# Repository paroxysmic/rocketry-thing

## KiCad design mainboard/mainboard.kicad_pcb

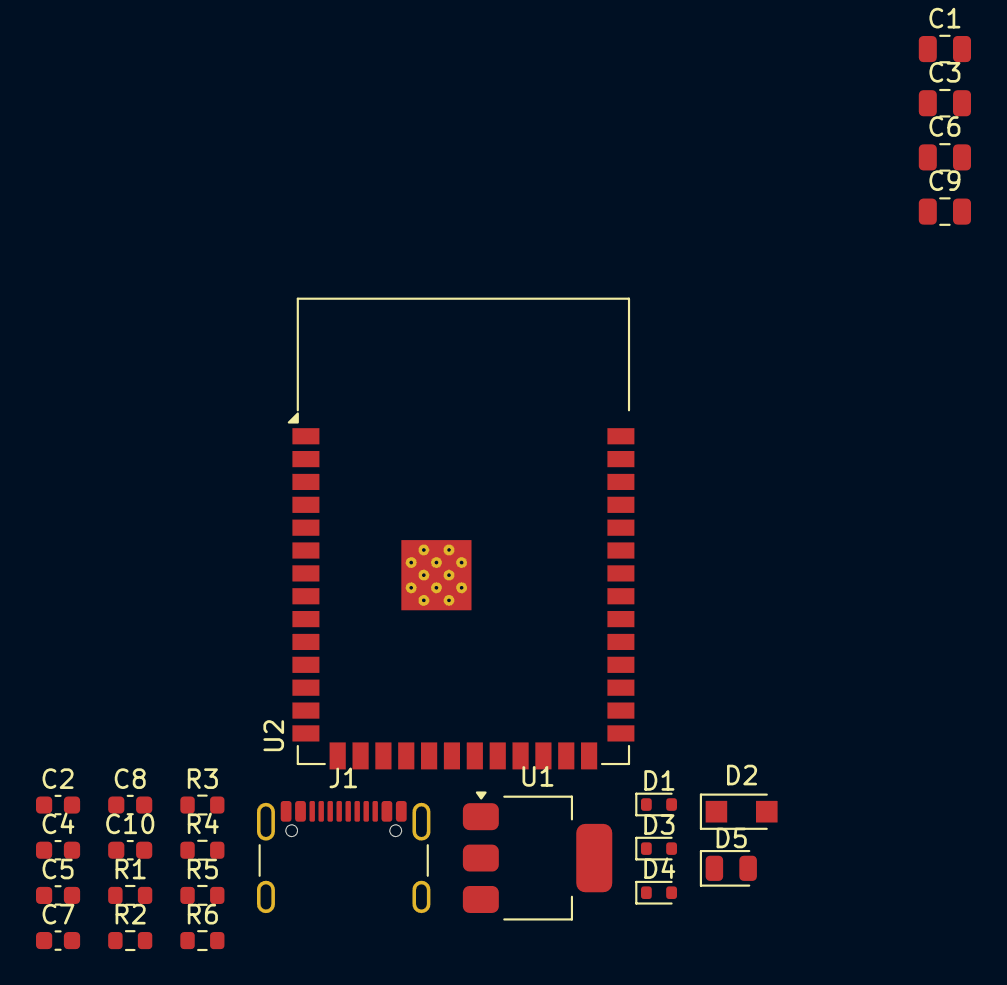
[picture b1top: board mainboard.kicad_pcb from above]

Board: 2 copper layers, 24 parts (0 on the bottom side), 11 nets, no tracks yet.

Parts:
C1, C3, C6, C9: 10uF; C_0805_2012Metric
C2, C4, C7, C8, C10: 100nF; C_0603_1608Metric
C5: 1uF; C_0603_1608Metric
D1, D3, D4: LESD5D5.0CT1G; D_SOD-523
D2: 1N5819HW; Nexperia_CFP3_SOD-123W
D5: LED; LED_0805_2012Metric
J1: USB_C_Receptacle_USB2.0_16P; USB_C_Receptacle_GCT_USB4105-xx-A_16P_TopMnt_Horizontal
R1, R5, R6: 10k; R_0603_1608Metric
R2, R3: 5.1k; R_0603_1608Metric
R4: 160; R_0603_1608Metric
U1: AMS1117-3.3; SOT-223-3_TabPin2
U2: ESP32-S3-WROOM-1

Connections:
D+: D4.2 (A2), J1.A6 (D+), J1.B6 (D+), U2.14 (USB_D+)
D-: D3.2 (A2), J1.A7 (D-), J1.B7 (D-), U2.13 (USB_D-)
GND: C1.2, C2.2, C3.2, C4.2, C5.2, C6.2, C7.2, C8.1, C9.1, C10.2, D1.1 (A1), D3.1 (A1), D4.1 (A1), J1.A1 (GND), J1.A12 (GND), J1.B1 (GND), J1.B12 (GND), J1.S1 (SHIELD), R2.1, R3.2, U1.1 (GND), U2.1 (GND), U2.40 (GND), U2.41 (GND)
GPIO0: C10.1, R6.2, U2.27 (IO0)
unnamed: D1.2 (A2), D2.2 (A), J1.A4 (VBUS), J1.A9 (VBUS), J1.B4 (VBUS), J1.B9 (VBUS)
unnamed: J1.A5 (CC1), R3.1
unnamed: J1.B5 (CC2), R2.2
unnamed: C5.1, C7.1, R1.2, R5.2, U2.3 (EN)
VCC_3.3V: C3.1, C4.1, U1.2 (VO)
VCC_3V3: C8.2, C9.2, R1.1, R5.1, R6.1, U2.2 (3V3)
VCC_5V: C1.1, C2.1, C6.1, D2.1 (K), U1.3 (VI)

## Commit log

2026-01-12 init
2026-01-16 updated mainboard
